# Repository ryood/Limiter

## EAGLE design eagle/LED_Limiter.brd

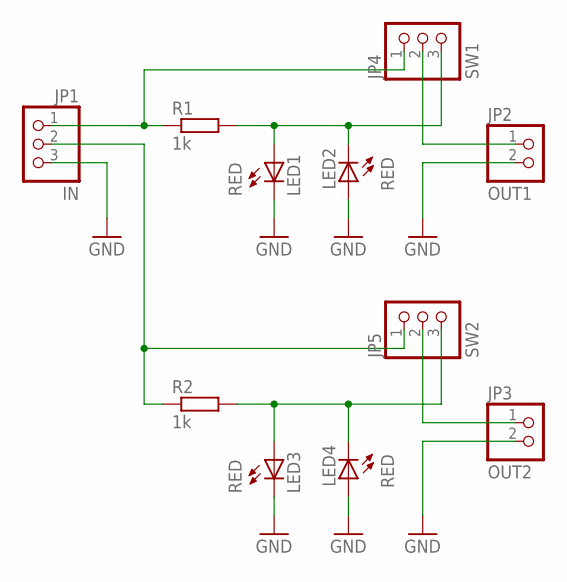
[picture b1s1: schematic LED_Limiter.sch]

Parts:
JP1: IN; 1X03
JP2: OUT1; 1X02
JP3: OUT2; 1X02
JP4: SW1; 1X03
JP5: SW2; 1X03
LED1, LED2, LED3, LED4: RED; LED3MM
R1, R2: 1k; 0207/7

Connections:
GND: JP1.3, JP2.2, JP3.2, LED1.K (C), LED2.A, LED3.K (C), LED4.A
IN: JP1.1, JP4.1, R1.1
unnamed: JP2.1, JP4.2
unnamed: JP4.3, LED1.A, LED2.K (C), R1.2
unnamed: JP5.3, LED3.A, LED4.K (C), R2.2
unnamed: JP3.1, JP5.2
unnamed: JP1.2, JP5.1, R2.1

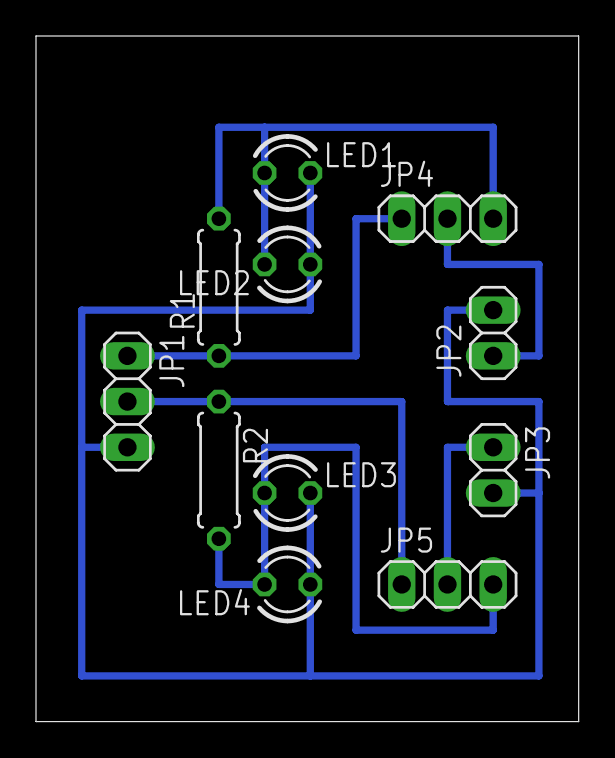
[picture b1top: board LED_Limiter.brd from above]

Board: 2 copper layers, 30.1 x 38.1 mm, 11 parts (0 on the bottom side), 7 nets.

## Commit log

2015-07-07 Add eagle files
